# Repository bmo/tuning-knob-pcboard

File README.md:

# tuning-knob-pcboard  
https://github.com/bmo/tuning-knob-pcboard

This is a KiCAD PC Board design for a tuning knob that works with PowerSDR and SmartSDR and Remote Ham Radio (RHR). Uses STM32 hardware. Find the software that works with this here: https://github.com/bmo/hwcontrol

## Features:
- 24ppr encoder
- multiple ways to build it
- uses mostly-available STM32F103 "Blue Pill" PC boards, may also work with newer, more powerful, more available, and cheaper (!?) "Black Pill" PCBs using STM32F4xx CPUs (with code changes)
- through-hole parts
- 20-30 minute assembly
- traces already supplied for future expansion for footswitch inputs, flash memory, SPI-based displays
- works with RHR, PowerSDR, SmartSDR when used in conjunction with https://github.com/bmo/hwcontrol

## Version 1:
Build it two ways:
- snap-action tactile switches and 3mm LEDs
- small tactile switches with built-in LEDs
- isolated pin 40 to not prohibit "Black Pill" from being plugged in

## Version 2 (in Progress):
- Cherry MX or compatible "buttons"
- RGB LEDs for illumination

## Future:
- With a composite USB Device providing two CDC (serial) devices, a solution that provides a Knob and a de-bounced footswitch

## References:
- KiCAD library / design for Cherry Switch + RGB : https://github.com/sszczep/Cherry-MX-Breakout-Board

## Contributions
Thanks to @cjtheham for BOM and documentation!

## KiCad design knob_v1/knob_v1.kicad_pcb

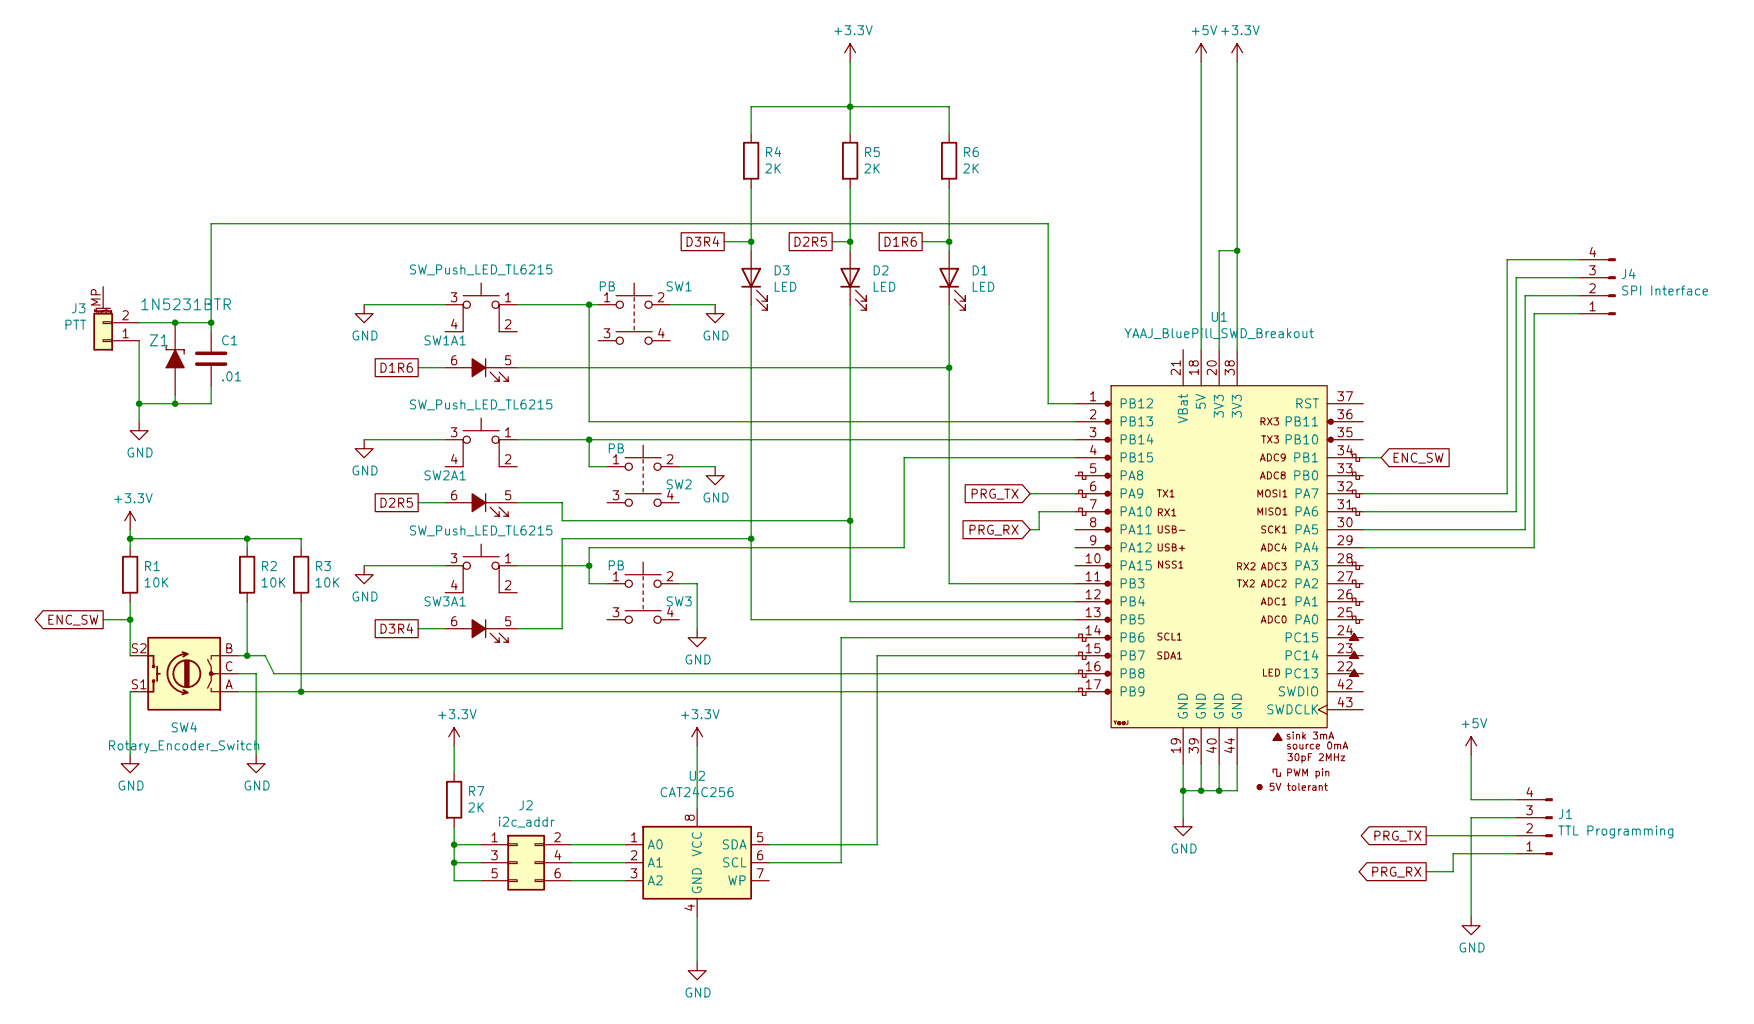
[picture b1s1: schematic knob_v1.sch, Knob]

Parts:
C1: .01; C_Disc_D3.0mm_W1.6mm_P2.50mm
D1, D2, D3: LED; LED_D3.0mm
J1: TTL Programming; PinHeader_1x04_P2.54mm_Vertical
J2: i2c_addr; PinHeader_2x04_P2.54mm_Vertical
J3: PTT; PinHeader_1x02_P2.54mm_Horizontal
J4: SPI Interface; PinHeader_1x04_P2.54mm_Vertical
R1, R2, R3: 10K; R_Axial_DIN0207_L6.3mm_D2.5mm_P7.62mm_Horizontal
R4, R5, R6, R7: 2K; R_Axial_DIN0207_L6.3mm_D2.5mm_P7.62mm_Horizontal
SW1, SW2, SW3: PB; SW_PUSH-12mm-corrected
SW1A1, SW2A1, SW3A1: SW_Push_LED_TL6215; TL6215V
SW4: Rotary_Encoder_Switch; RotaryEncoder_Alps_EC12E-Switch_Vertical_H20mm
U1: YAAJ_BluePill_SWD_Breakout; YAAJ_BluePill_SWD_1
U2: CAT24C256; SOIC8-1.27-5X4MM
Z1: 1N5231BTR; DO-35; MPN 1N5231BTR; Digi-Key_PN 1N5231BFSCT-ND

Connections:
+3V3: R1.1, R2.1, R3.1, R4.1, R5.1, R6.1, R7.1, U1.20 (3V3), U1.38 (3V3), U2.8 (VCC)
+5V: J1.4, U1.18 (5V)
D1R6: D1.2 (A), R6.2, SW1A1.6 (A)
D2R5: D2.2 (A), R5.2, SW2A1.6 (A)
D3R4: D3.2 (A), R4.2, SW3A1.6 (A)
ENC_SW: R1.2, SW4.S2, U1.34 (PB1)
GND: C1.2, J1.3, J3.1, SW1.2, SW1A1.3, SW2.2, SW2A1.3, SW3.2, SW3A1.3, SW4.C, SW4.S1, U1.19 (GND), U1.39 (GND), U1.40 (GND), U1.44 (GND), U2.4 (GND), Z1.A
unnamed: C1.1, J3.2, U1.1 (PB12), Z1.K
unnamed: D1.1 (K), SW1A1.5 (K), U1.11 (PB3)
unnamed: D2.1 (K), SW2A1.5 (K), U1.12 (PB4)
unnamed: D3.1 (K), SW3A1.5 (K), U1.13 (PB5)
unnamed: J2.1, J2.3, J2.5, R7.2
unnamed: J2.2, U2.1 (A0)
unnamed: J2.4, U2.2 (A1)
unnamed: J2.6, U2.3 (A2)
unnamed: J4.1, U1.29 (PA4)
unnamed: J4.2, U1.30 (PA5)
unnamed: J4.3, U1.31 (PA6)
unnamed: J4.4, U1.32 (PA7)
unnamed: R2.2, SW4.B, U1.16 (PB8)
unnamed: R3.2, SW4.A, U1.17 (PB9)
unnamed: SW1.1, SW1A1.1, U1.2 (PB13)
unnamed: SW2.1, SW2A1.1, U1.3 (PB14)
unnamed: SW3.1, SW3A1.1, U1.4 (PB15)
unnamed: U1.14 (PB6), U2.6 (SCL)
unnamed: U1.15 (PB7), U2.5 (SDA)
PRG_RX: J1.1, U1.7 (PA10)
PRG_TX: J1.2, U1.6 (PA9)

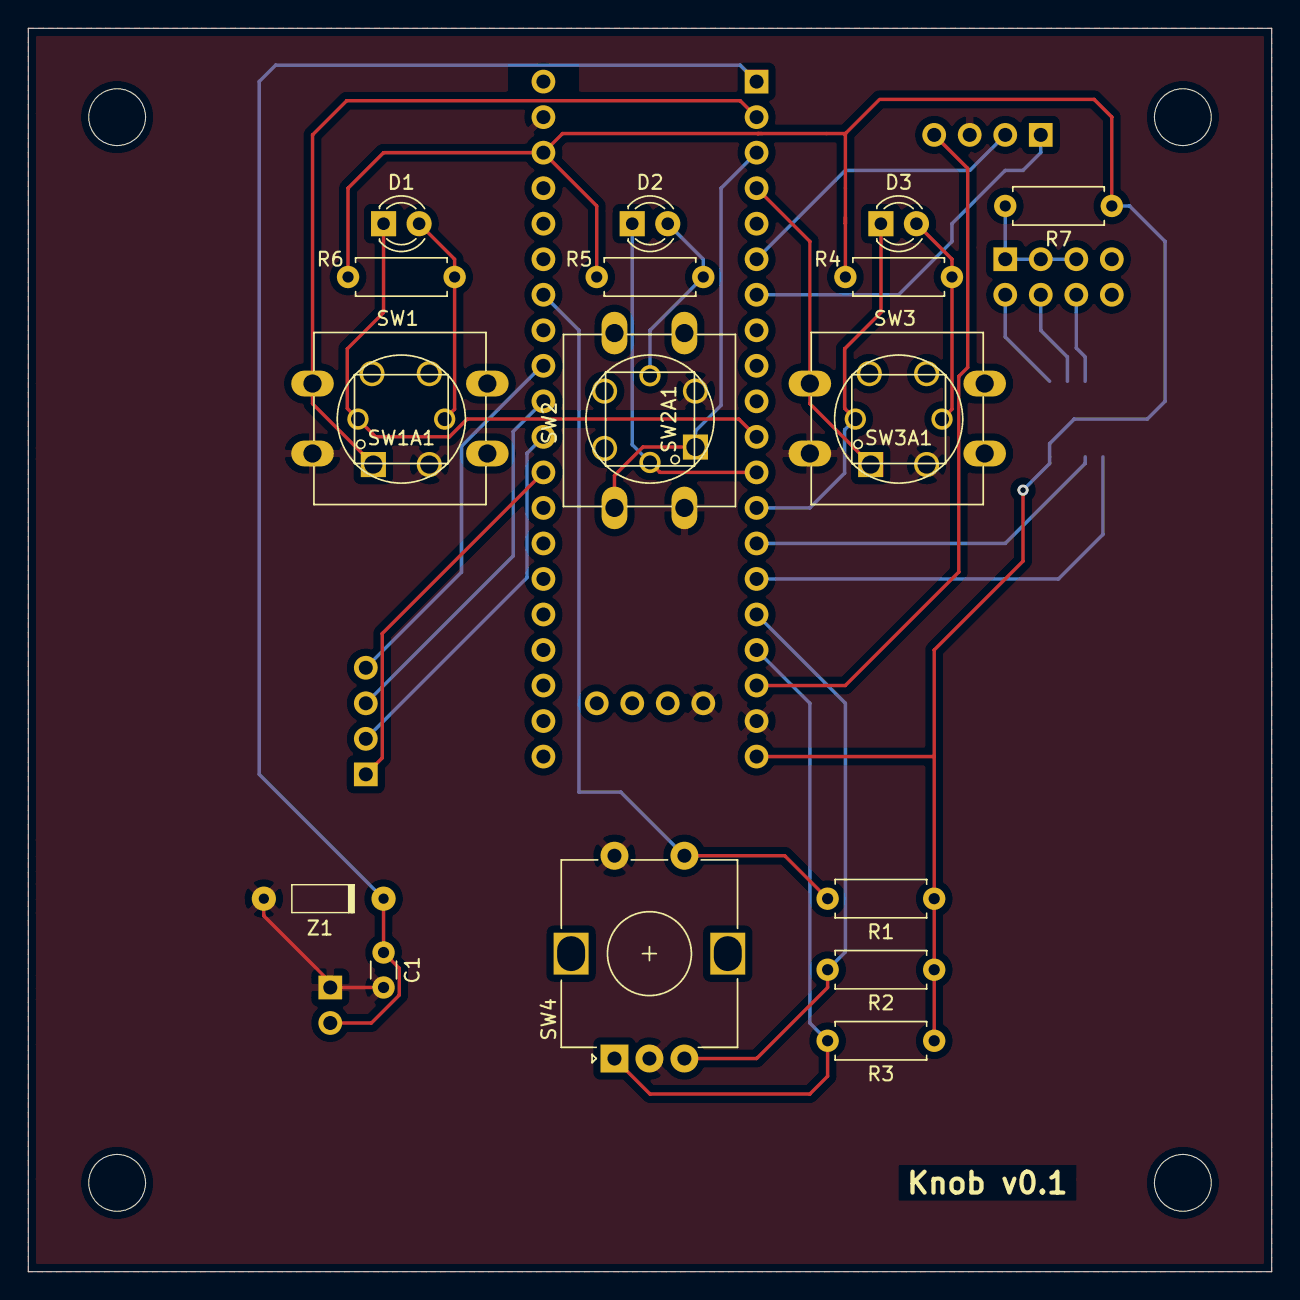
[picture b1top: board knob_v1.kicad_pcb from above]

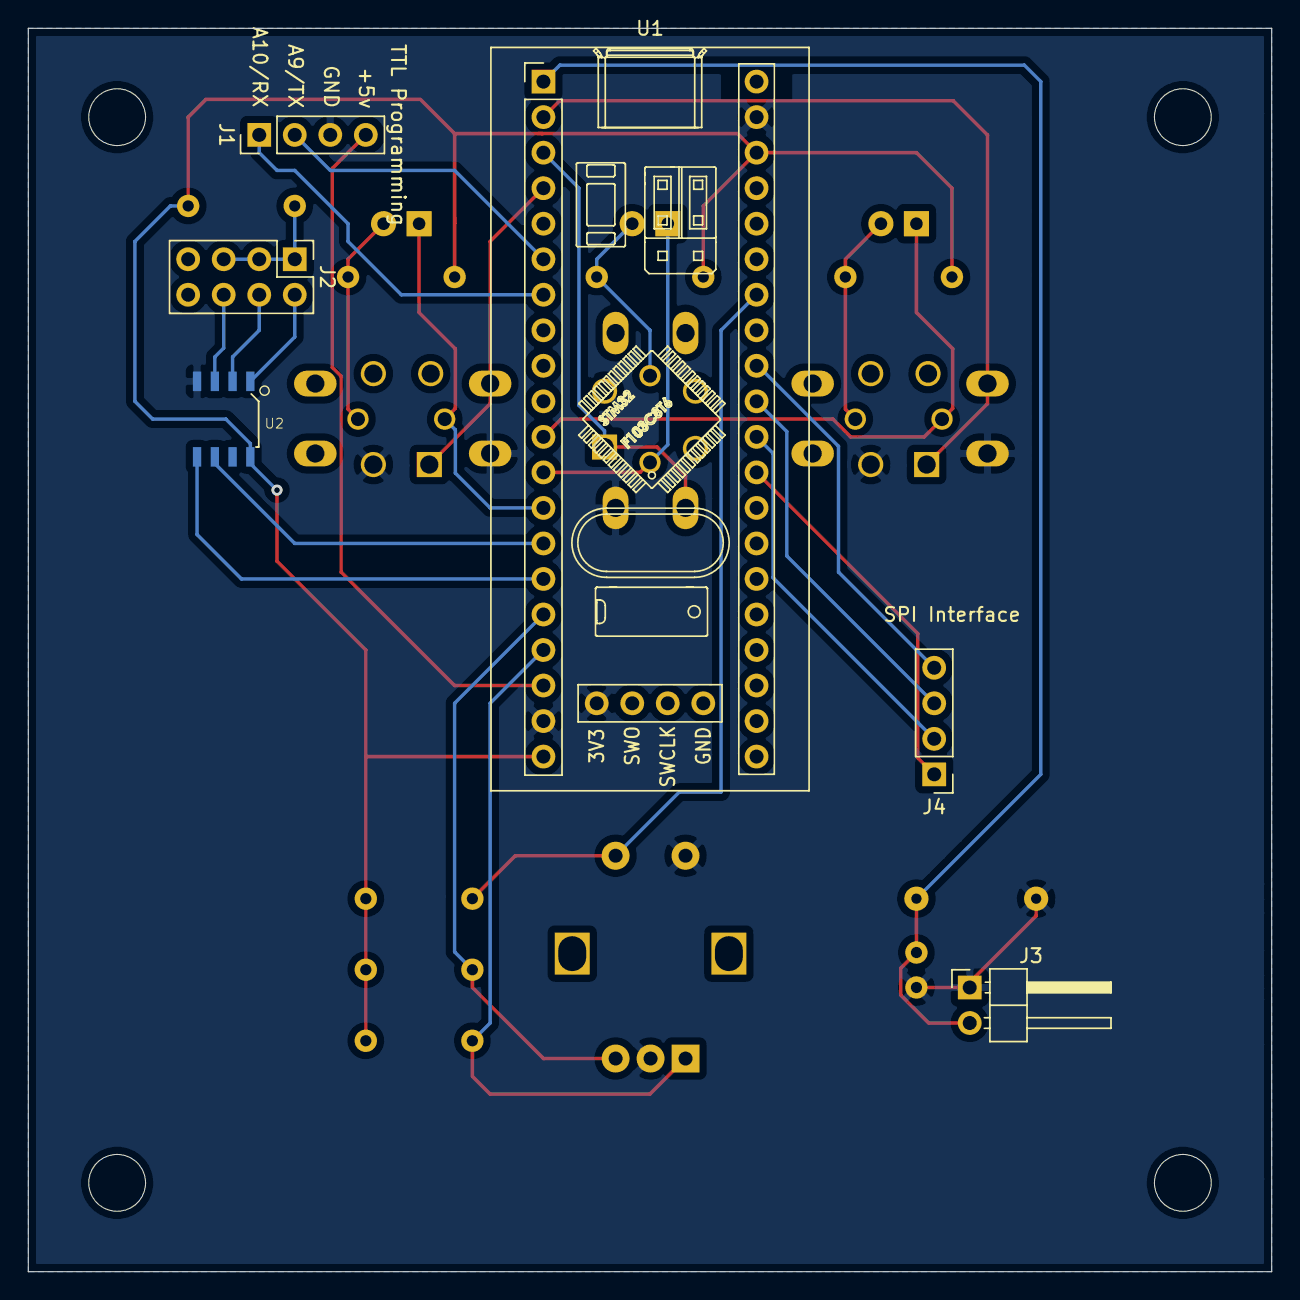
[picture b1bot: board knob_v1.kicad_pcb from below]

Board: 2 copper layers, 88.9 x 88.9 mm, 25 parts (6 on the bottom side), 28 nets.

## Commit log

2021-06-27 commit plots
2022-02-10 Added pictures of V1 knobs
2022-08-03 initial documentation
2022-08-03 assembly note + image
2022-08-03 link to code
